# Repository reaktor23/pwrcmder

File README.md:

# pwrcmder
Reaktor23 Power Commander https://reaktor23.org/projects/pwrcmdr2/

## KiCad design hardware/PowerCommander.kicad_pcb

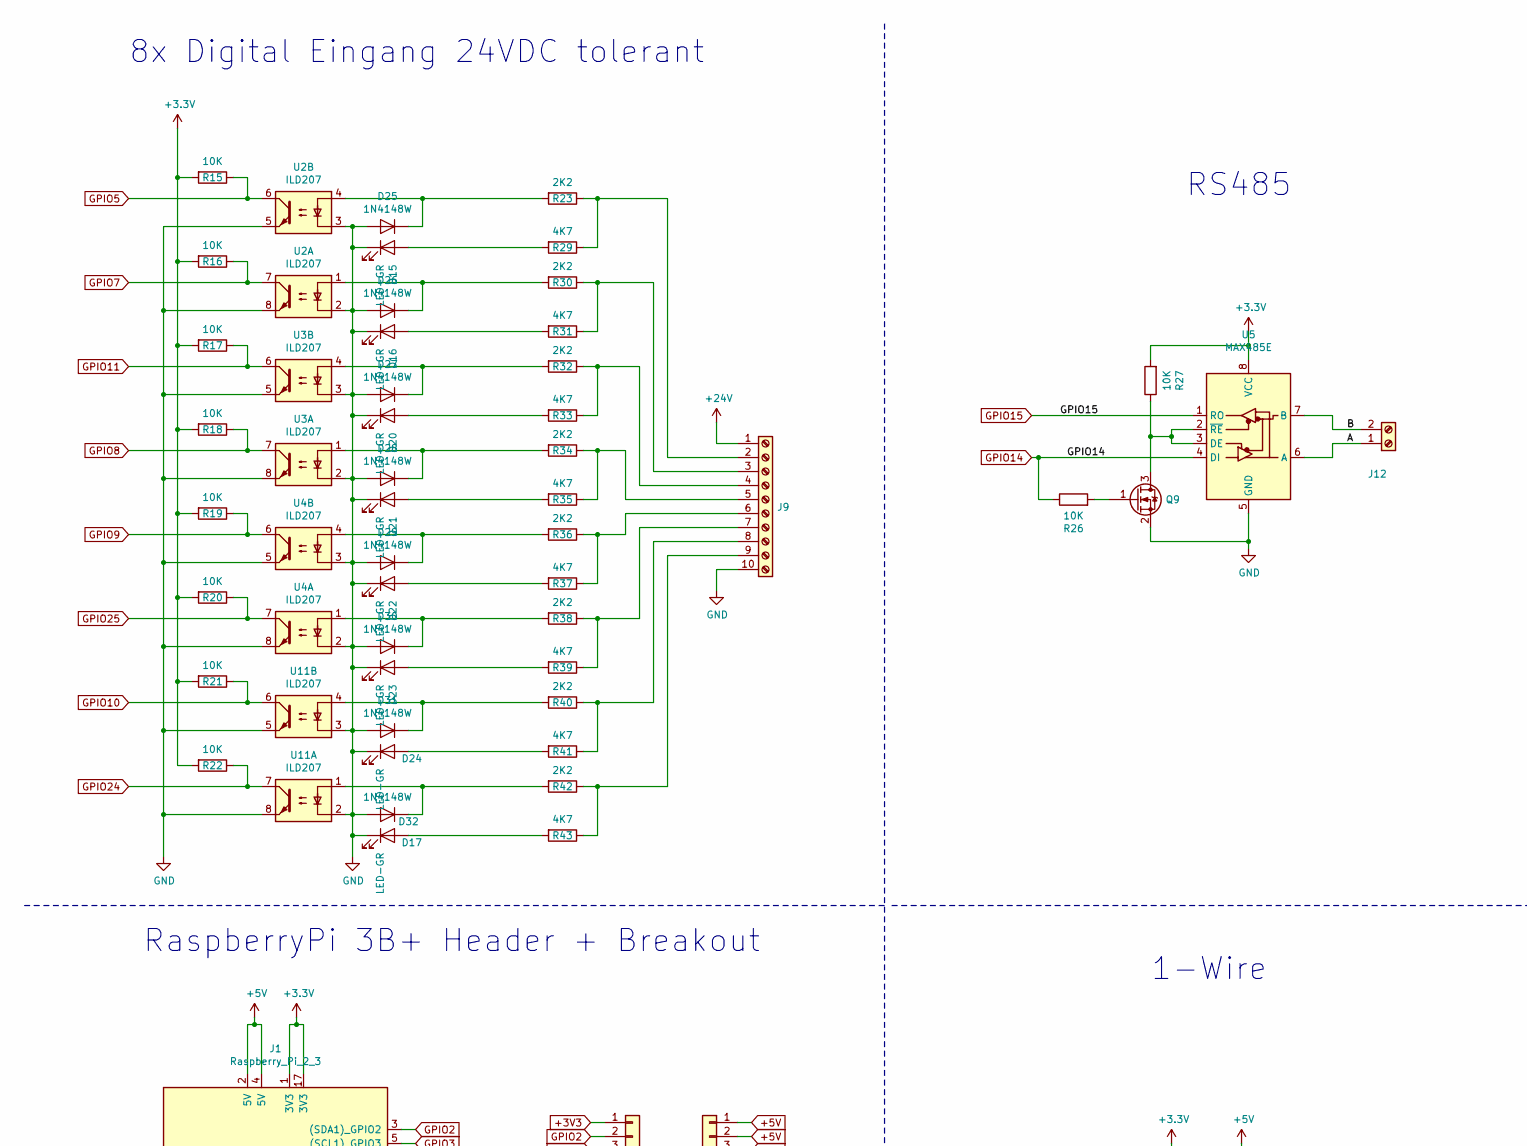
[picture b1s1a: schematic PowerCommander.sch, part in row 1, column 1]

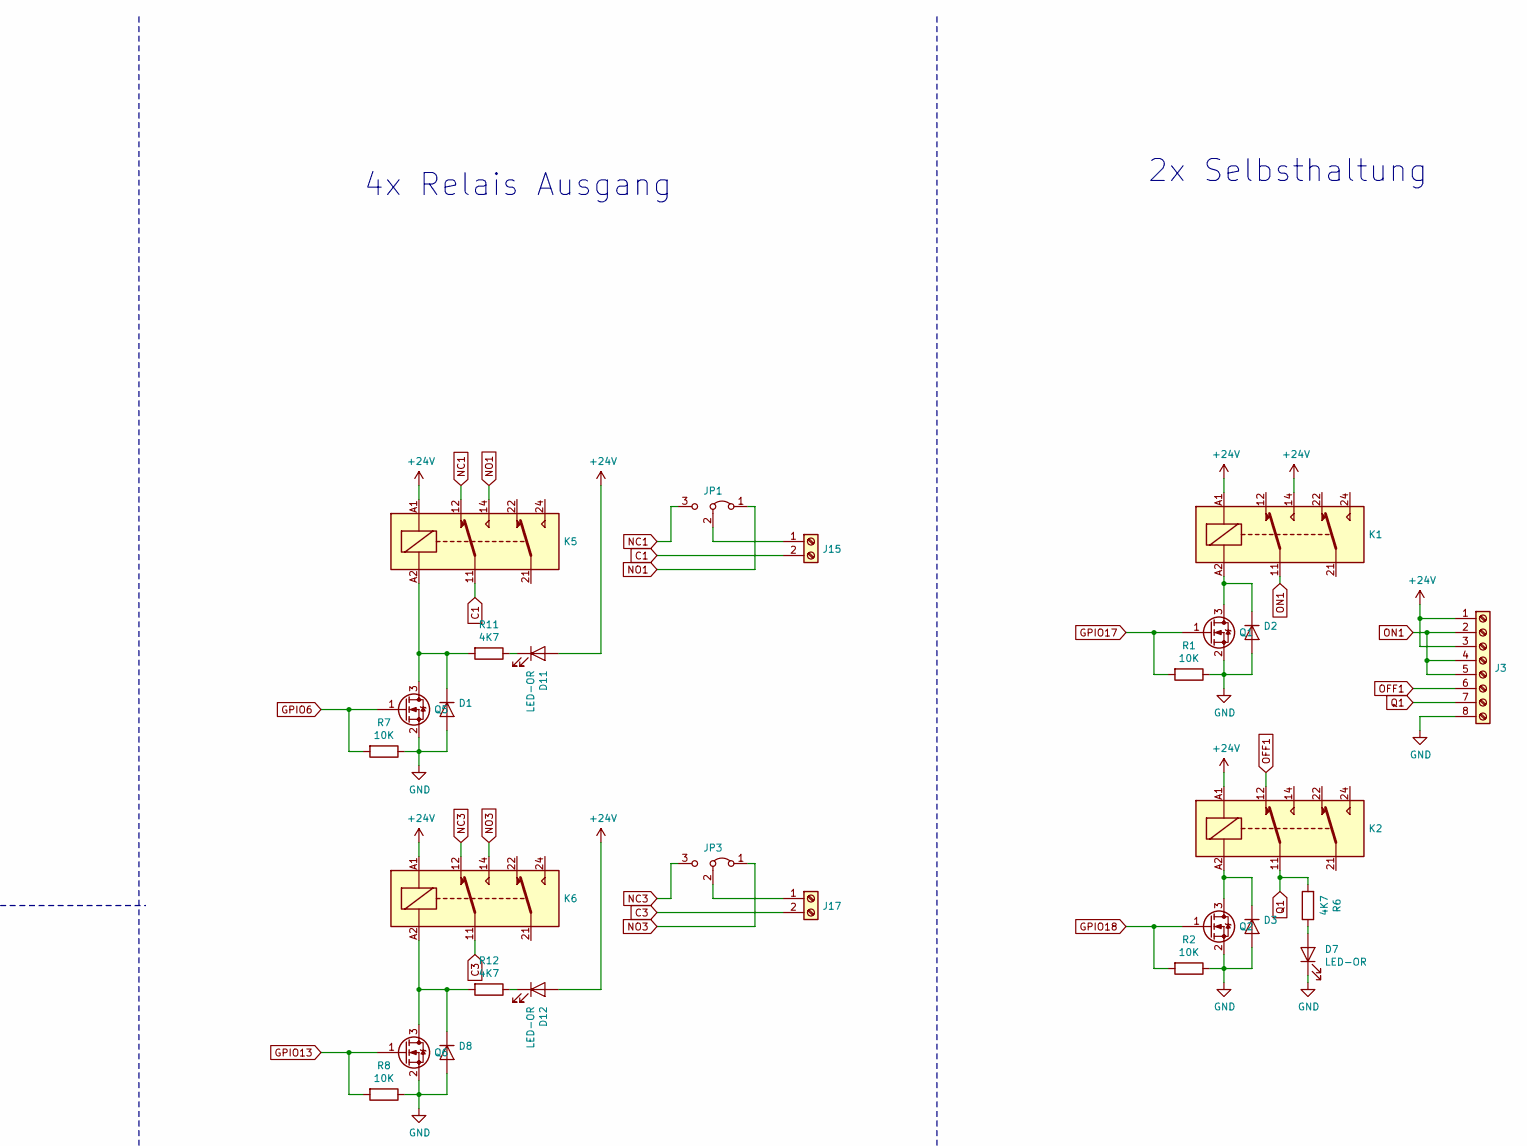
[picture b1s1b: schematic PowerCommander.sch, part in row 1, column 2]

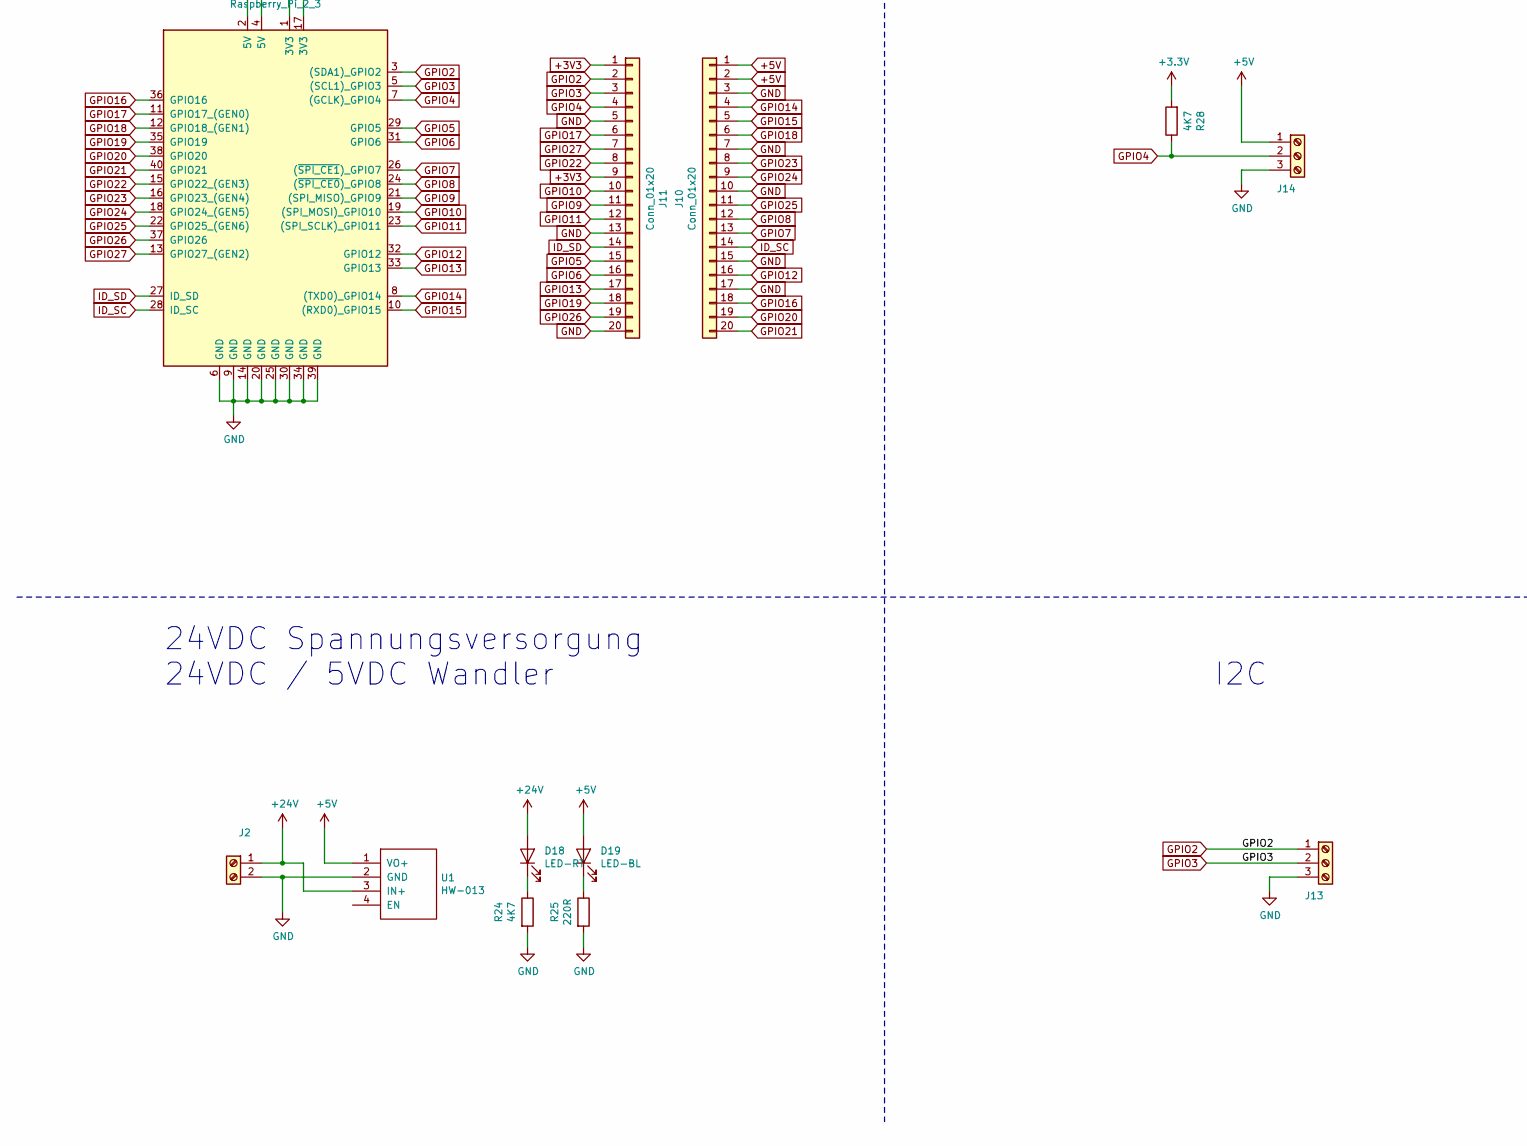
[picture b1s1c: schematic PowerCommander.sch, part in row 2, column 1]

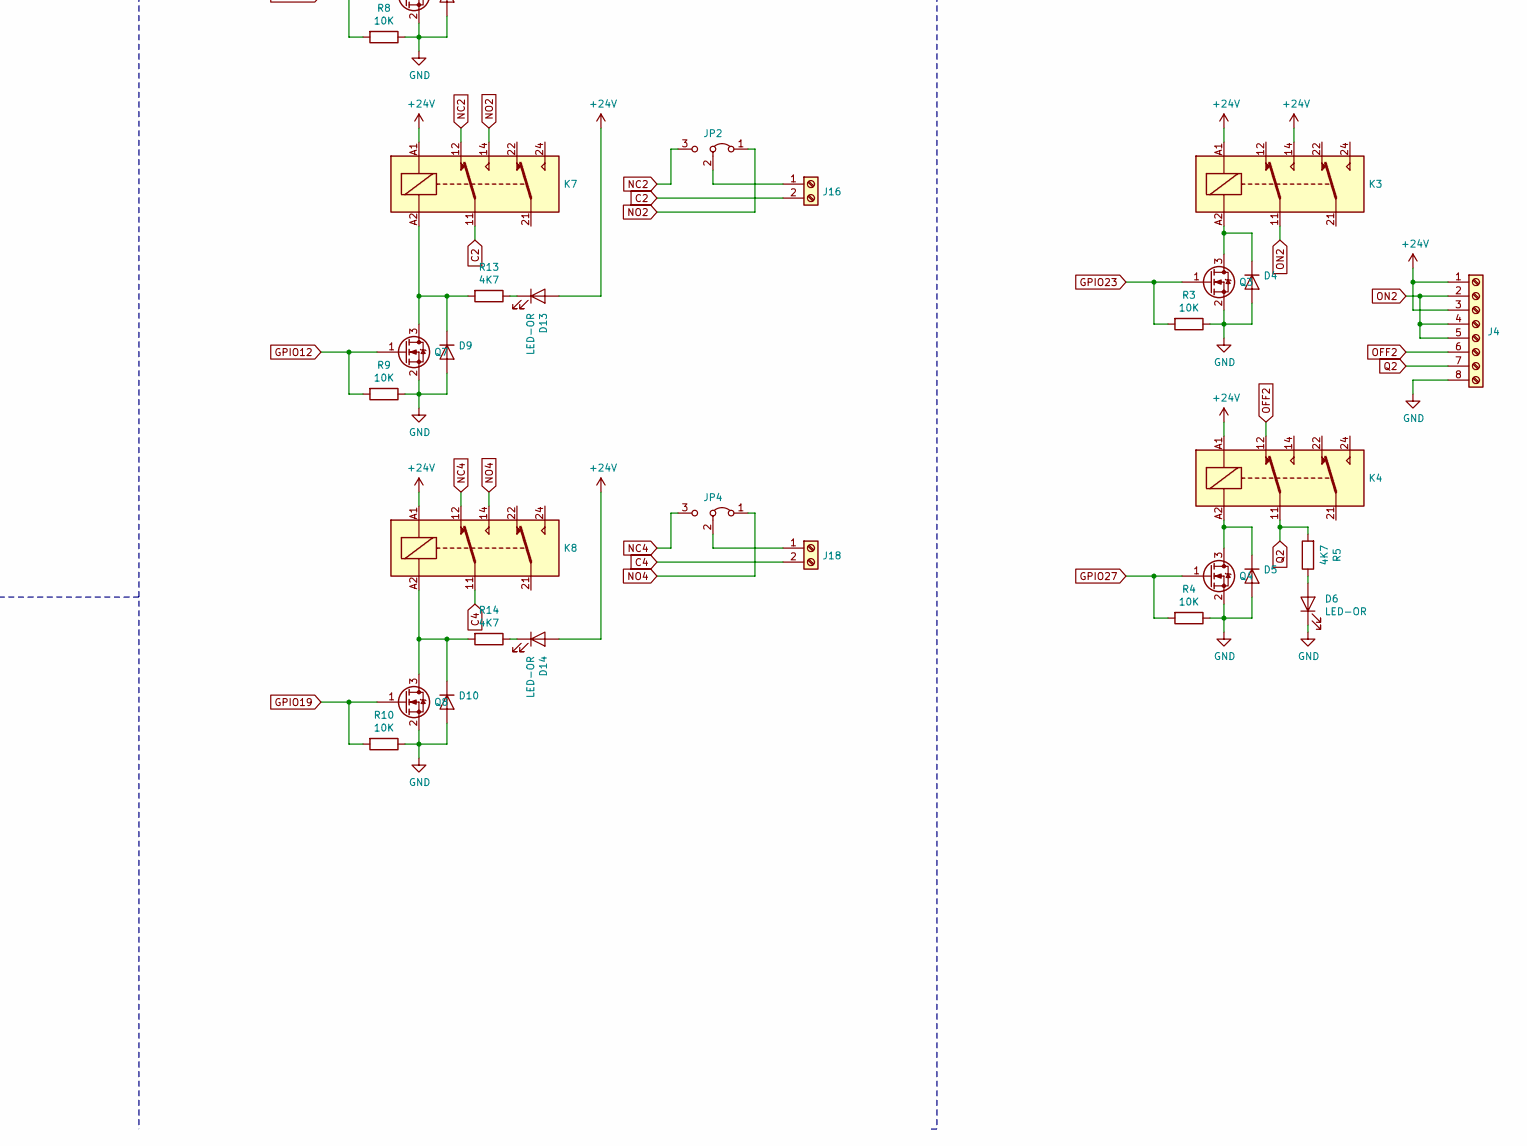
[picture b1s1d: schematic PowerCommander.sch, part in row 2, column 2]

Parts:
D1, D2, D3, D4, D5, D8, D9, D10, D25, D26, D27, D28, D29, D30, D31, D32: 1N4148W; D_SOD-123
D6, D7, D11, D12, D13, D14: LED-OR; LED_0603_HandSoldering
D15, D16, D17, D20, D21, D22, D23, D24: LED-GR; LED_0603_HandSoldering
D18: LED-RT; LED_0603_HandSoldering
D19: LED-BL; LED_0603_HandSoldering
J1: Raspberry_Pi_2_3; Socket_Strip_Straight_2x20_Pitch2.54mm
J2, J12, J15, J16, J17, J18: Screw_Terminal_01x02; PhoenixContact_MC_1,5_2-G-3.81_1x02_P3.81mm_Horizontal
J3, J4: Screw_Terminal_01x08; PhoenixContact_MC_1,5_8-G-3.81_1x08_P3.81mm_Horizontal
J9: Screw_Terminal_01x10; PhoenixContact_MC_1,5_10-G-3.81_1x10_P3.81mm_Horizontal
J10, J11: Conn_01x20; Pin_Header_Straight_1x20_Pitch2.54mm
J13, J14: Screw_Terminal_01x03; PhoenixContact_MC_1,5_3-G-3.81_1x03_P3.81mm_Horizontal
JP1, JP2, JP3, JP4: Jumper_3_Bridged12; SolderJumper-3_P1.3mm_Bridged12_Pad1.0x1.5mm
K1, K2, K3, K4: FINDER-30.22; Relay_SPDT_Finder_32.22
K5, K6, K7, K8: FINDER-30.22; Relay_SPST_Finder_32.21-x300
Q1, Q2, Q3, Q4, Q5, Q6, Q7, Q8, Q9: BSS138; SOT-23
R1, R2, R3, R4, R7, R8, R9, R10, R15, R16, R17, R18, R19, R20, R21, R22, R26, R27: 10K; R_0805_HandSoldering
R5, R6, R11, R12, R13, R14, R24, R28, R29, R31, R33, R35, R37, R39, R41, R43: 4K7; R_1206
R23, R30, R32, R34, R36, R38, R40, R42: 2K2; R_1206
R25: 220R; R_1206
U1: HW-013
U2, U3, U4, U11: ILD207; SOIC-8_3.9x4.9mm_P1.27mm
U5: MAX485E; SOIC-8_3.9x4.9mm_P1.27mm

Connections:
+5V: D19.2 (A), J1.2 (5V), J1.4 (5V), J10.1, J10.2, J14.1, U1.1 (VO+)
+24V: D11.2 (A), D12.2 (A), D13.2 (A), D14.2 (A), D18.2 (A), J2.1, J3.1, J3.3, J4.1, J4.3, J9.1, K1.14, K1.A1, K2.A1, K3.14, K3.A1, K4.A1, K5.A1, K6.A1, K7.A1, K8.A1, U1.3 (IN+)
/A: J12.1, U5.6 (A)
/B: J12.2, U5.7 (B)
C1: J15.2, K5.11
C2: J16.2, K7.11
C3: J17.2, K6.11
C4: J18.2, K8.11
GND: D1.2 (A), D2.2 (A), D3.2 (A), D4.2 (A), D5.2 (A), D6.1 (K), D7.1 (K), D8.2 (A), D9.2 (A), D10.2 (A), D15.1 (K), D16.1 (K), D17.1 (K), D20.1 (K), D21.1 (K), D22.1 (K), D23.1 (K), D24.1 (K), D25.2 (A), D26.2 (A), D27.2 (A), D28.2 (A), D29.2 (A), D30.2 (A), D31.2 (A), D32.2 (A), J1.6 (GND), J1.9 (GND), J1.14 (GND), J1.20 (GND), J1.25 (GND), J1.30 (GND), J1.34 (GND), J1.39 (GND), J2.2, J3.8, J4.8, J9.10, J10.3, J10.7, J10.10, J10.15, J10.17, J11.5, J11.13, J11.20, J13.3, J14.3, Q1.2 (S), Q2.2 (S), Q3.2 (S), Q4.2 (S), Q5.2 (S), Q6.2 (S), Q7.2 (S), Q8.2 (S), Q9.2 (S), R1.1, R2.1, R3.1, R4.1, R7.1, R8.1, R9.1, R10.1, R24.2, R25.2, U1.2 (GND), U2.2, U2.3, U2.5, U2.8, U3.2, U3.3, U3.5, U3.8, U4.2, U4.3, U4.5, U4.8, U5.5 (GND), U11.2, U11.3, U11.5, U11.8
GPIO2: J1.3 ((SDA1)_GPIO2), J11.2, J13.1
GPIO3: J1.5 ((SCL1)_GPIO3), J11.3, J13.2
GPIO4: J1.7 ((GCLK)_GPIO4), J11.4, J14.2, R28.1
GPIO5: J1.29 (GPIO5), J11.15, R15.1, U2.6
GPIO6: J1.31 (GPIO6), J11.16, Q5.1 (G), R7.2
GPIO7: J1.26 ((~SPI_CE1~)_GPIO7), J10.13, R16.1, U2.7
GPIO8: J1.24 ((~SPI_CE0~)_GPIO8), J10.12, R18.1, U3.7
GPIO9: J1.21 ((SPI_MISO)_GPIO9), J11.11, R19.1, U4.6
GPIO10: J1.19 ((SPI_MOSI)_GPIO10), J11.10, R21.1, U11.6
GPIO11: J1.23 ((SPI_SCLK)_GPIO11), J11.12, R17.1, U3.6
GPIO12: J1.32 (GPIO12), J10.16, Q7.1 (G), R9.2
GPIO13: J1.33 (GPIO13), J11.17, Q6.1 (G), R8.2
GPIO14: J1.8 ((TXD0)_GPIO14), J10.4, R26.1, U5.4 (DI)
GPIO15: J1.10 ((RXD0)_GPIO15), J10.5, U5.1 (RO)
GPIO16: J1.36 (GPIO16), J10.18
GPIO17: J1.11 (GPIO17_(GEN0)), J11.6, Q1.1 (G), R1.2
GPIO18: J1.12 (GPIO18_(GEN1)), J10.6, Q2.1 (G), R2.2
GPIO19: J1.35 (GPIO19), J11.18, Q8.1 (G), R10.2
GPIO20: J1.38 (GPIO20), J10.19
GPIO21: J1.40 (GPIO21), J10.20
GPIO22: J1.15 (GPIO22_(GEN3)), J11.8
GPIO23: J1.16 (GPIO23_(GEN4)), J10.8, Q3.1 (G), R3.2
GPIO24: J1.18 (GPIO24_(GEN5)), J10.9, R22.1, U11.7
GPIO25: J1.22 (GPIO25_(GEN6)), J10.11, R20.1, U4.7
GPIO26: J1.37 (GPIO26), J11.19
GPIO27: J1.13 (GPIO27_(GEN2)), J11.7, Q4.1 (G), R4.2
ID_SC: J1.28 (ID_SC), J10.14
ID_SD: J1.27 (ID_SD), J11.14
NC1: JP1.3 (B), K5.12
NC2: JP2.3 (B), K7.12
NC3: JP3.3 (B), K6.12
NC4: JP4.3 (B), K8.12
NO1: JP1.1 (A), K5.14
NO2: JP2.1 (A), K7.14
NO3: JP3.1 (A), K6.14
NO4: JP4.1 (A), K8.14
unnamed: D1.1 (K), K5.A2, Q5.3 (D), R11.2
unnamed: D2.1 (K), K1.A2, Q1.3 (D)
unnamed: D3.1 (K), K2.A2, Q2.3 (D)
unnamed: D4.1 (K), K3.A2, Q3.3 (D)
unnamed: D5.1 (K), K4.A2, Q4.3 (D)
unnamed: D6.2 (A), R5.1
unnamed: D7.2 (A), R6.1
unnamed: D8.1 (K), K6.A2, Q6.3 (D), R12.2
unnamed: D9.1 (K), K7.A2, Q7.3 (D), R13.2
unnamed: D10.1 (K), K8.A2, Q8.3 (D), R14.2
unnamed: D11.1 (K), R11.1
unnamed: D12.1 (K), R12.1
unnamed: D13.1 (K), R13.1
unnamed: D14.1 (K), R14.1
unnamed: D15.2 (A), R29.2
unnamed: D16.2 (A), R31.2
unnamed: D17.2 (A), R43.2
unnamed: D18.1 (K), R24.1
unnamed: D19.1 (K), R25.1
unnamed: D20.2 (A), R33.2
unnamed: D21.2 (A), R35.2
unnamed: D22.2 (A), R37.2
unnamed: D23.2 (A), R39.2
unnamed: D24.2 (A), R41.2
unnamed: D25.1 (K), R23.2, U2.4
unnamed: D26.1 (K), R30.2, U2.1
unnamed: D27.1 (K), R32.2, U3.4
unnamed: D28.1 (K), R34.2, U3.1
unnamed: D29.1 (K), R36.2, U4.4
unnamed: D30.1 (K), R38.2, U4.1
unnamed: D31.1 (K), R40.2, U11.4
unnamed: D32.1 (K), R42.2, U11.1
unnamed: J9.2, R23.1, R29.1
unnamed: J9.3, R30.1, R31.1
unnamed: J9.4, R32.1, R33.1
unnamed: J9.5, R34.1, R35.1
unnamed: J9.6, R36.1, R37.1
unnamed: J9.7, R38.1, R39.1
unnamed: J9.8, R40.1, R41.1
unnamed: J9.9, R42.1, R43.1
unnamed: J15.1, JP1.2 (C)
unnamed: J16.1, JP2.2 (C)
unnamed: J17.1, JP3.2 (C)
unnamed: J18.1, JP4.2 (C)
unnamed: Q9.1 (G), R26.2
unnamed: Q9.3 (D), R27.1, U5.2 (~RE), U5.3 (DE)
OFF1: J3.6, K2.12
OFF2: J4.6, K4.12
ON1: J3.2, J3.4, J3.5, K1.11
ON2: J4.2, J4.4, J4.5, K3.11
Q1: J3.7, K2.11, R6.2
Q2: J4.7, K4.11, R5.2

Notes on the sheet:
2x Selbsthaltung
4x Relais Ausgang
RS485
1-Wire
I2C
24VDC Spannungsversorgung 24VDC / 5VDC Wandler
RaspberryPi 3B+ Header + Breakout
8x Digital Eingang 24VDC tolerant

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
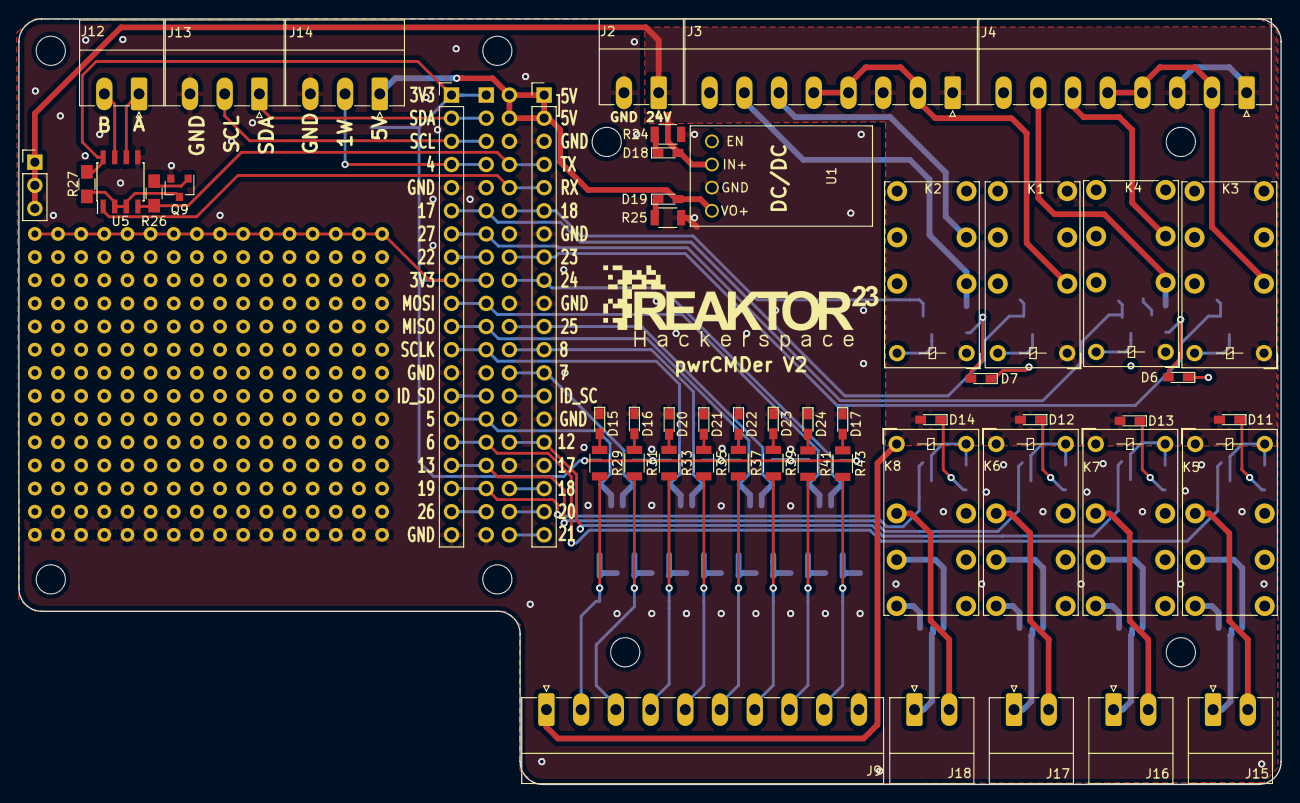
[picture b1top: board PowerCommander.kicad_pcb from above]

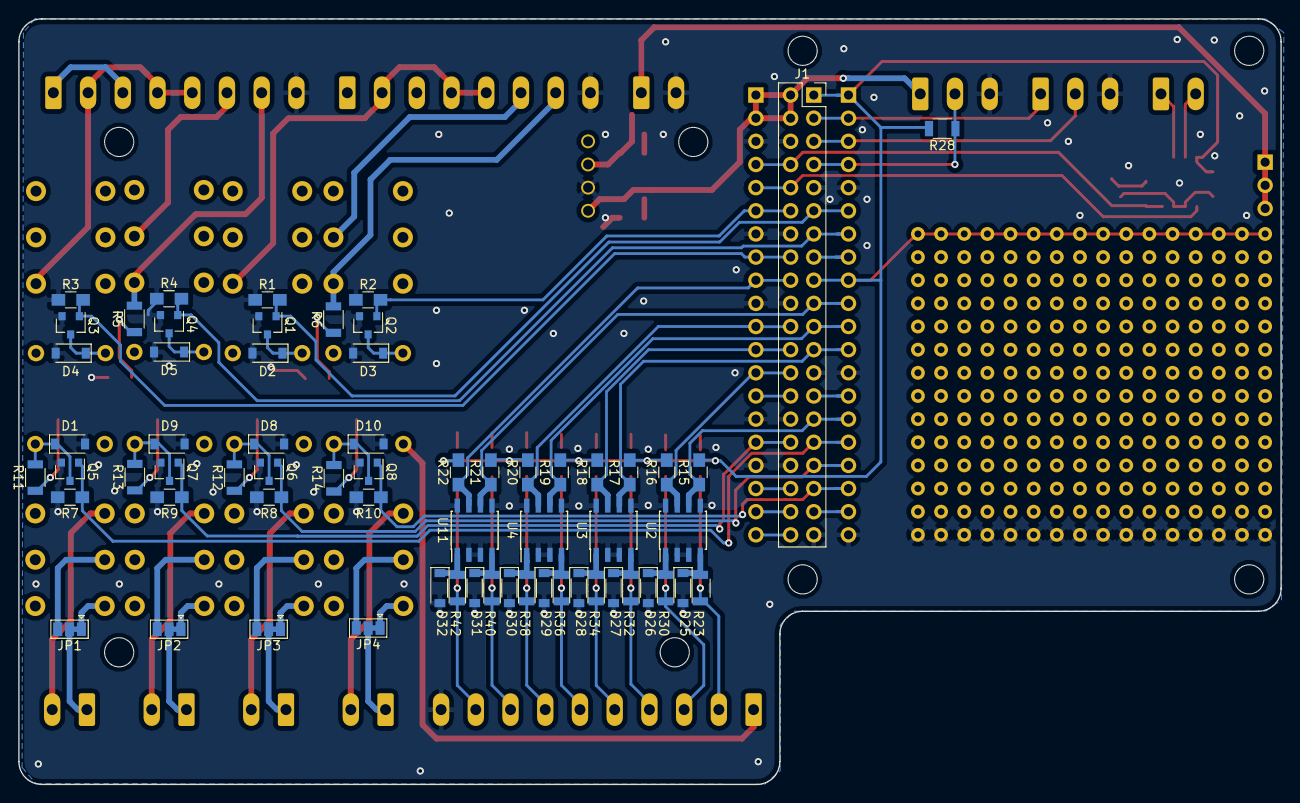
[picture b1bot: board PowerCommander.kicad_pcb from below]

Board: 2 copper layers, 138.5 x 84.0 mm, 116 parts (64 on the bottom side), 98 nets.

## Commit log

2020-10-07 add hardware design files
2020-10-07 add PDF with front and back of the board
2020-10-13 updated config
2021-08-20 Fix email address
2021-10-19 replaced template based hacker counter with python script to allow long term statistics
2021-10-19 synced repo with pwrcmder config
2021-10-19 Updated to new sensor name
    Updated the old sensor name, sensor.member_count, to the new sensor name, sensor.hackers.
